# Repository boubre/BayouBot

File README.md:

BayouBot
========

Software for controlling an inexpensive educational robot.

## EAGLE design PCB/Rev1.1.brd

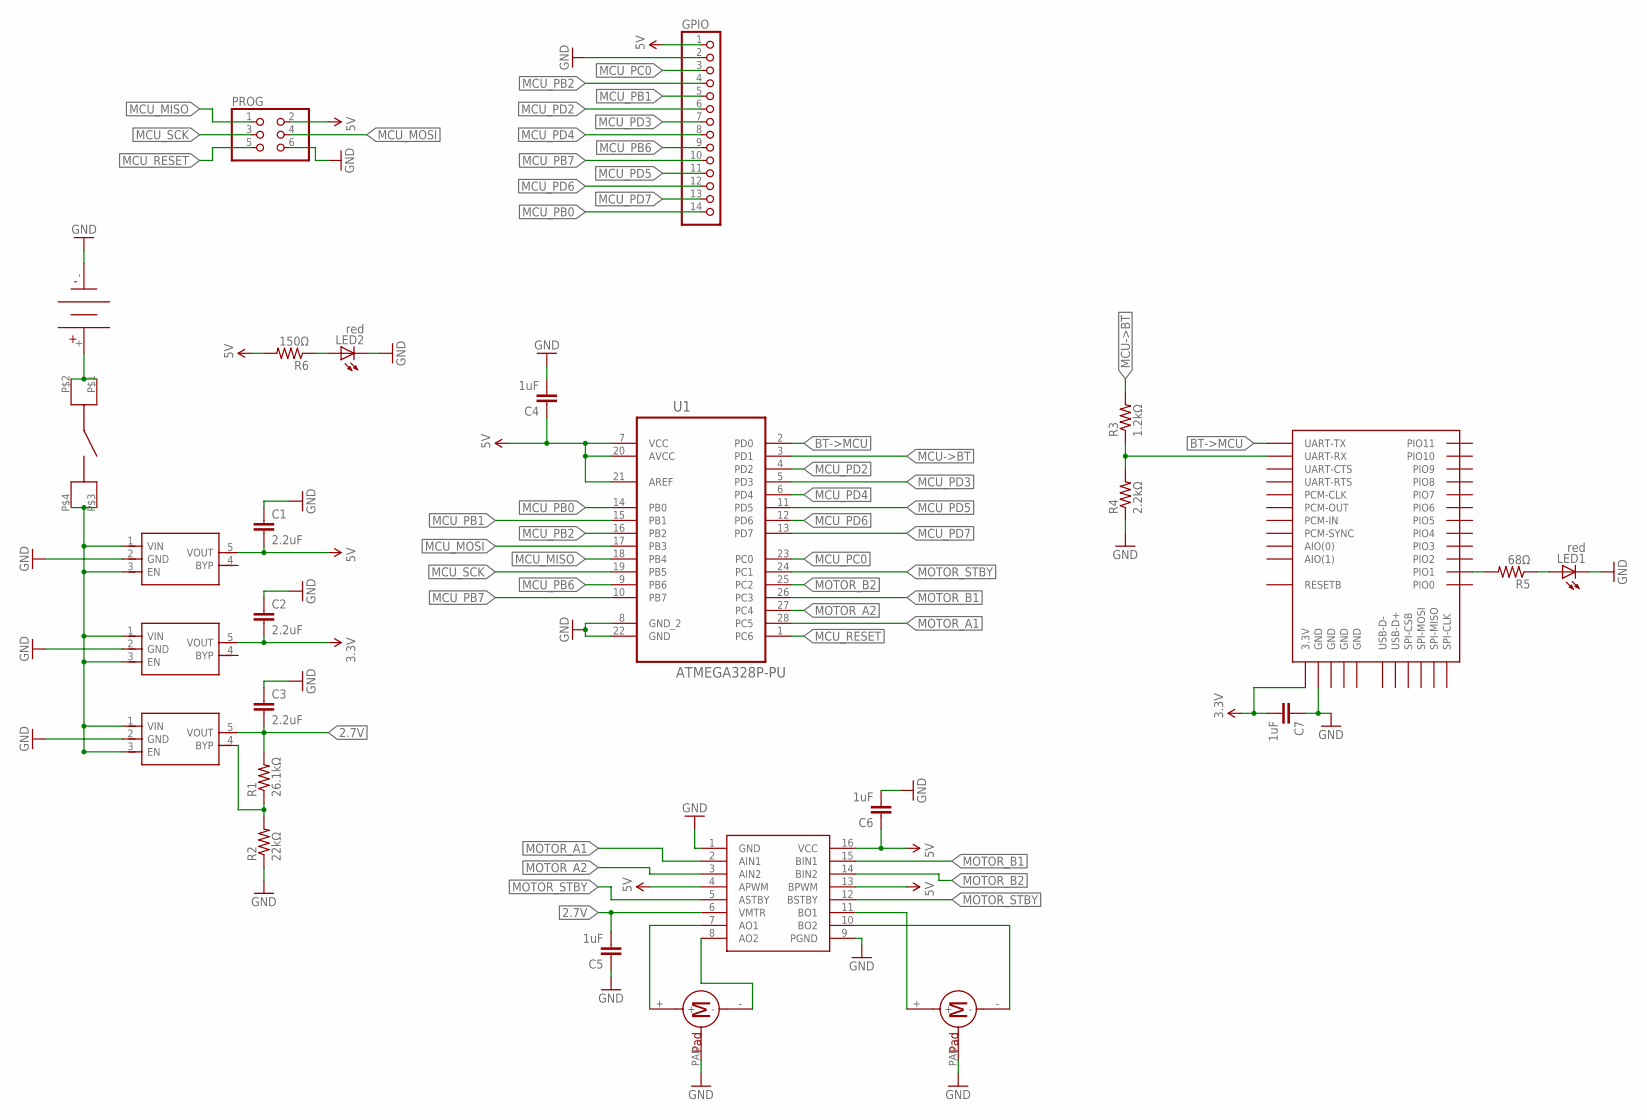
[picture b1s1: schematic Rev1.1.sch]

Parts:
C1, C2, C3: 2.2uF; 0805
C4, C5, C6, C7: 1uF; 0805
GPIO: PINHD-1X14; 1X14
LED1, LED2: red; CHIP-LED0805
PROG: PINHD-2X3; 2X03
R1: 26.1kΩ; 0805
R2: 22kΩ; 0805
R3: 1.2kΩ; 0805
R4: 2.2kΩ; 0805
R5: 68Ω; 0805
R6: 150Ω; 0805
U1: ATMEGA328P-PU; DIP254P762X457-28
U2: BT; BTM400_6B
U3: SMD_H-BRIDGE; SSOP16
U$1: 20MM_COIN
U$2: POWER_BTN
U$3: 5V Reg; SOT23-5
U$4: 3.3V Reg; SOT23-5
U$5: 2.7V Reg; SOT23-5
U$7, U$8: PICO_VIBE_MTR

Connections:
2.7V: C3.2, C5.2, R1.2, U3.6 (VMTR), U$5.5 (VOUT)
3.3V: C2.2, C7.2, U2.3.3V, U$4.5 (VOUT)
5V: C1.2, C4.1, C6.1, GPIO.1, PROG.2, R6.2, U1.7 (VCC), U1.20 (AVCC), U1.21 (AREF), U3.4 (APWM), U3.13 (BPWM), U3.16 (VCC), U$3.5 (VOUT)
BT->MCU: U1.2 (PD0), U2.UART-TX
GND: C1.1, C2.1, C3.1, C4.2, C5.1, C6.2, C7.1, GPIO.2, LED1.C, LED2.C, PROG.6, R2.1, R4.1, U1.8 (GND_2), U1.22 (GND), U2.GND@1 (GND), U2.GND@2 (GND), U2.GND@3 (GND), U2.GND@4 (GND), U3.1 (GND), U3.9 (PGND), U$1.-, U$3.2 (GND), U$4.2 (GND), U$5.2 (GND), U$7.PAD, U$8.PAD
MCU->BT: R3.2, U1.3 (PD1)
MCU_MISO: PROG.1, U1.18 (PB4)
MCU_MOSI: PROG.4, U1.17 (PB3)
MCU_PB0: GPIO.14, U1.14 (PB0)
MCU_PB1: GPIO.5, U1.15 (PB1)
MCU_PB2: GPIO.4, U1.16 (PB2)
MCU_PB6: GPIO.9, U1.9 (PB6)
MCU_PB7: GPIO.10, U1.10 (PB7)
MCU_PC0: GPIO.3, U1.23 (PC0)
MCU_PD2: GPIO.6, U1.4 (PD2)
MCU_PD3: GPIO.7, U1.5 (PD3)
MCU_PD4: GPIO.8, U1.6 (PD4)
MCU_PD5: GPIO.11, U1.11 (PD5)
MCU_PD6: GPIO.12, U1.12 (PD6)
MCU_PD7: GPIO.13, U1.13 (PD7)
MCU_RESET: PROG.5, U1.1 (PC6)
MCU_SCK: PROG.3, U1.19 (PB5)
MOTOR_A1: U1.28 (PC5), U3.2 (AIN1)
MOTOR_A2: U1.27 (PC4), U3.3 (AIN2)
MOTOR_B1: U1.26 (PC3), U3.15 (BIN1)
MOTOR_B2: U1.25 (PC2), U3.14 (BIN2)
MOTOR_STBY: U1.24 (PC1), U3.5 (ASTBY), U3.12 (BSTBY)
unnamed: U$1.+, U$2.P$1, U$2.P$2
unnamed: U$2.P$3, U$2.P$4, U$3.1 (VIN), U$3.3 (EN), U$4.1 (VIN), U$4.3 (EN), U$5.1 (VIN), U$5.3 (EN)
unnamed: R1.1, R2.2, U$5.4 (BYP)
unnamed: U3.7 (AO1), U$7.+
unnamed: U3.8 (AO2), U$7.-
unnamed: U3.11 (BO1), U$8.+
unnamed: U3.10 (BO2), U$8.-
unnamed: R3.1, R4.2, U2.UART-RX
unnamed: R5.2, U2.PIO(1) (PIO1)
unnamed: LED1.A, R5.1
unnamed: LED2.A, R6.1

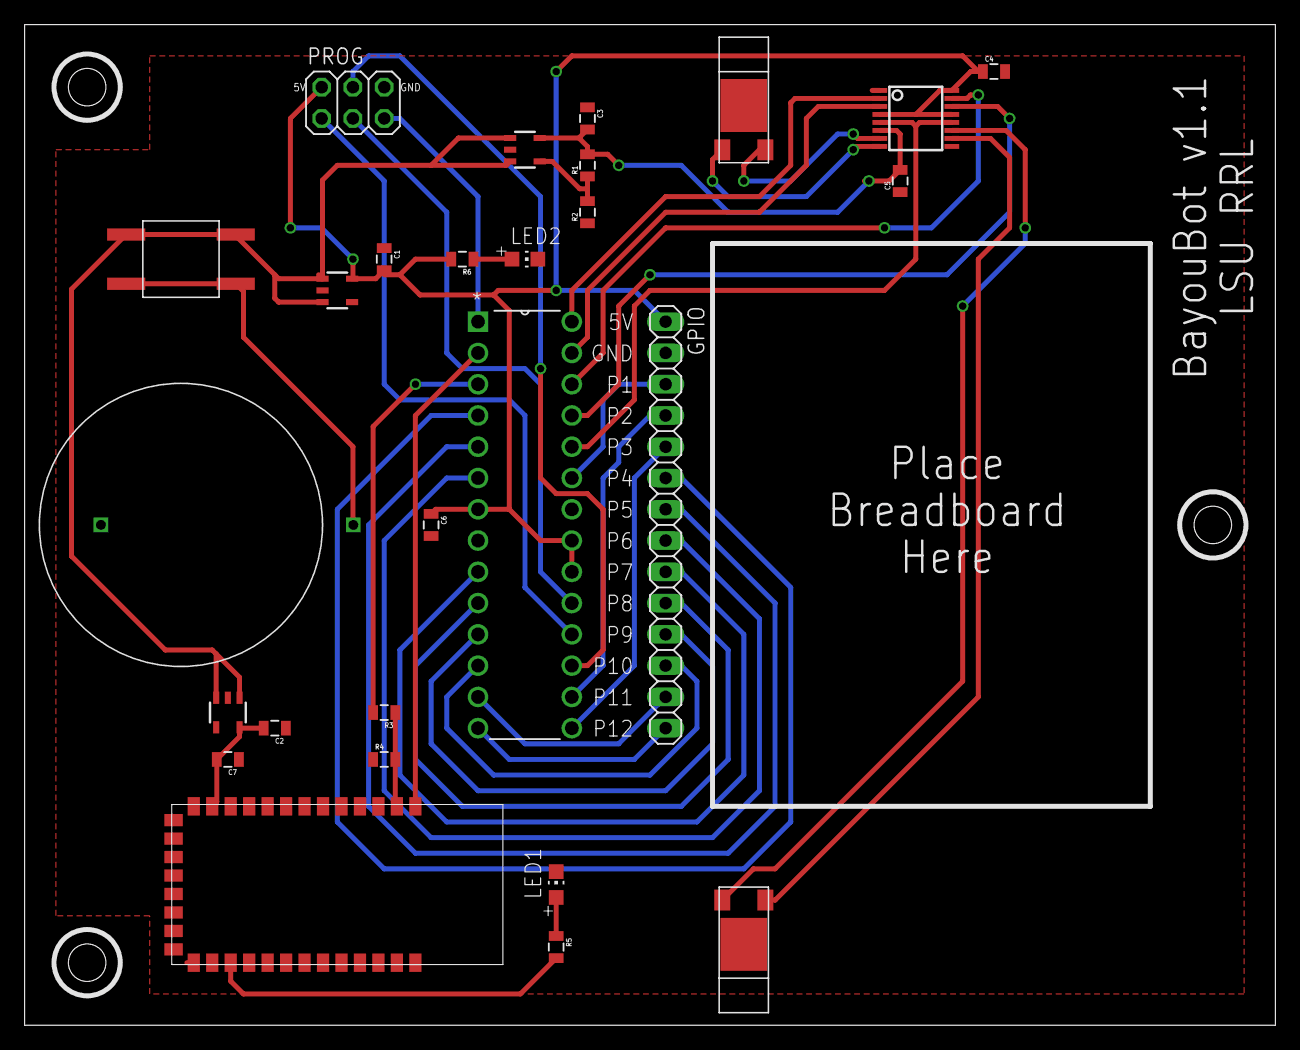
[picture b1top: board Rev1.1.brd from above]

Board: 2 copper layers, 101.6 x 81.3 mm, 27 parts (0 on the bottom side), 38 nets.

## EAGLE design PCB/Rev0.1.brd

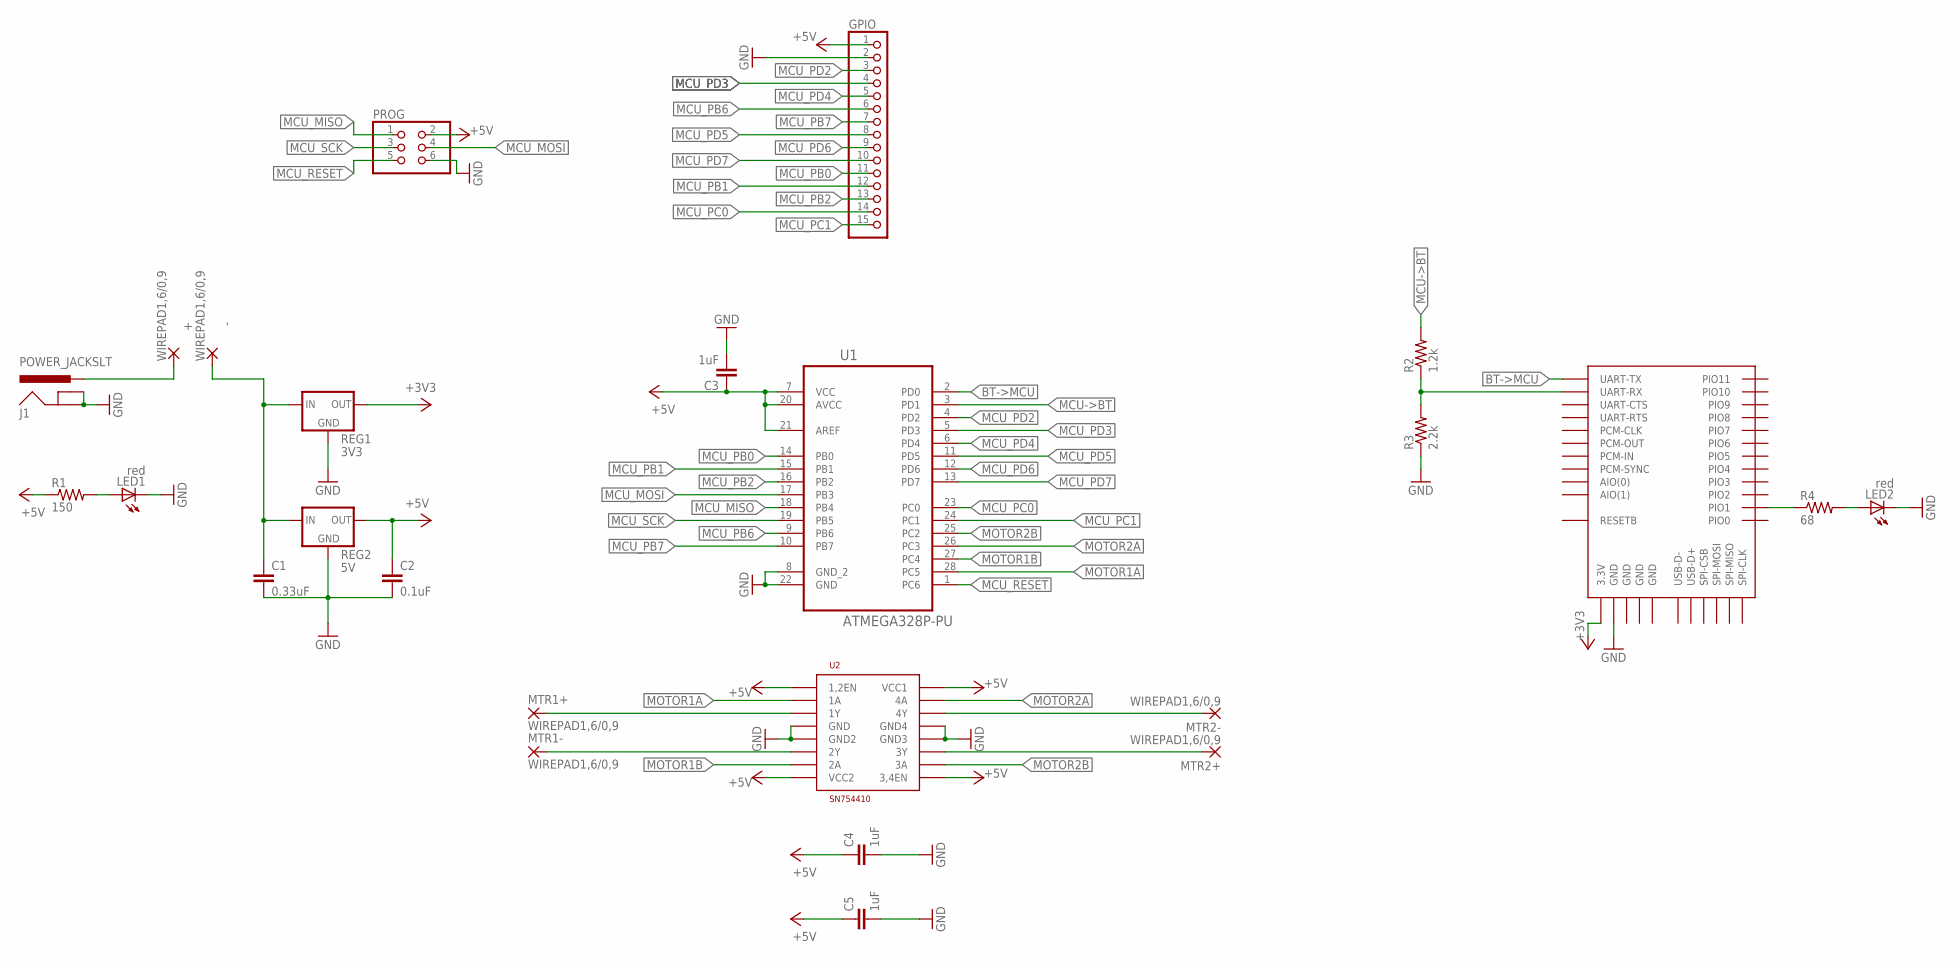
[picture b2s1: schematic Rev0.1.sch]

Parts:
+: WIREPAD1,6/0,9; 1,6/0,9
-: WIREPAD1,6/0,9; 1,6/0,9
C1: 0.33uF; 0805
C2: 0.1uF; 0805
C3, C4, C5: 1uF; 0805
GPIO: PINHD-1X15; 1X15
J1: POWER_JACKSLT; POWER_JACK_SLOT
LED1, LED2: red; CHIP-LED0805
MTR1+, MTR1-, MTR2+, MTR2-: WIREPAD1,6/0,9; 1,6/0,9
PROG: PINHD-2X3; 2X03
R1: 150; R0805
R2: 1.2k; R0805
R3: 2.2k; R0805
R4: 68; R0805
REG1: 3V3; TO220V
REG2: 5V; TO220V
U1: ATMEGA328P-PU; DIP254P762X457-28
U2: H-BRIDGE; DIP16
U$1: BTM400_6B

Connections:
+3V3: REG1.3 (OUT), U$1.3.3V
+5V: C2.1, C3.1, C4.1, C5.1, GPIO.1, PROG.2, R1.1, REG2.3 (OUT), U1.7 (VCC), U1.20 (AVCC), U1.21 (AREF), U2.P$1 (1,2EN), U2.P$8 (VCC2), U2.P$9 (3,4EN), U2.P$16 (VCC1)
BT->MCU: U1.2 (PD0), U$1.UART-TX
GND: C1.2, C2.2, C3.2, C4.2, C5.2, GPIO.2, J1.GND@1 (GNDBREAK), J1.GND@2 (GND), LED1.C, LED2.C, PROG.6, R3.1, REG1.2 (GND), REG2.2 (GND), U1.8 (GND_2), U1.22 (GND), U2.P$4 (GND), U2.P$5 (GND2), U2.P$12 (GND3), U2.P$13 (GND4), U$1.GND@1 (GND), U$1.GND@2 (GND), U$1.GND@3 (GND), U$1.GND@4 (GND)
MCU->BT: R2.2, U1.3 (PD1)
MCU_MISO: PROG.1, U1.18 (PB4)
MCU_MOSI: PROG.4, U1.17 (PB3)
MCU_PB0: GPIO.11, U1.14 (PB0)
MCU_PB1: GPIO.12, U1.15 (PB1)
MCU_PB2: GPIO.13, U1.16 (PB2)
MCU_PB6: GPIO.6, U1.9 (PB6)
MCU_PB7: GPIO.7, U1.10 (PB7)
MCU_PC0: GPIO.14, U1.23 (PC0)
MCU_PC1: GPIO.15, U1.24 (PC1)
MCU_PD2: GPIO.3, U1.4 (PD2)
MCU_PD3: GPIO.4, U1.5 (PD3)
MCU_PD4: GPIO.5, U1.6 (PD4)
MCU_PD5: GPIO.8, U1.11 (PD5)
MCU_PD6: GPIO.9, U1.12 (PD6)
MCU_PD7: GPIO.10, U1.13 (PD7)
MCU_RESET: PROG.5, U1.1 (PC6)
MCU_SCK: PROG.3, U1.19 (PB5)
MOTOR1A: U1.28 (PC5), U2.P$2 (1A)
MOTOR1B: U1.27 (PC4), U2.P$7 (2A)
MOTOR2A: U1.26 (PC3), U2.P$15 (4A)
MOTOR2B: U1.25 (PC2), U2.P$10 (3A)
unnamed: -.1, C1.1, REG1.1 (IN), REG2.1 (IN)
unnamed: LED1.A, R1.2
unnamed: +.1, J1.PWR
unnamed: MTR1+.1, U2.P$3 (1Y)
unnamed: MTR1-.1, U2.P$6 (2Y)
unnamed: MTR2-.1, U2.P$14 (4Y)
unnamed: MTR2+.1, U2.P$11 (3Y)
unnamed: R2.1, R3.2, U$1.UART-RX
unnamed: R4.1, U$1.PIO(1) (PIO1)
unnamed: LED2.A, R4.2

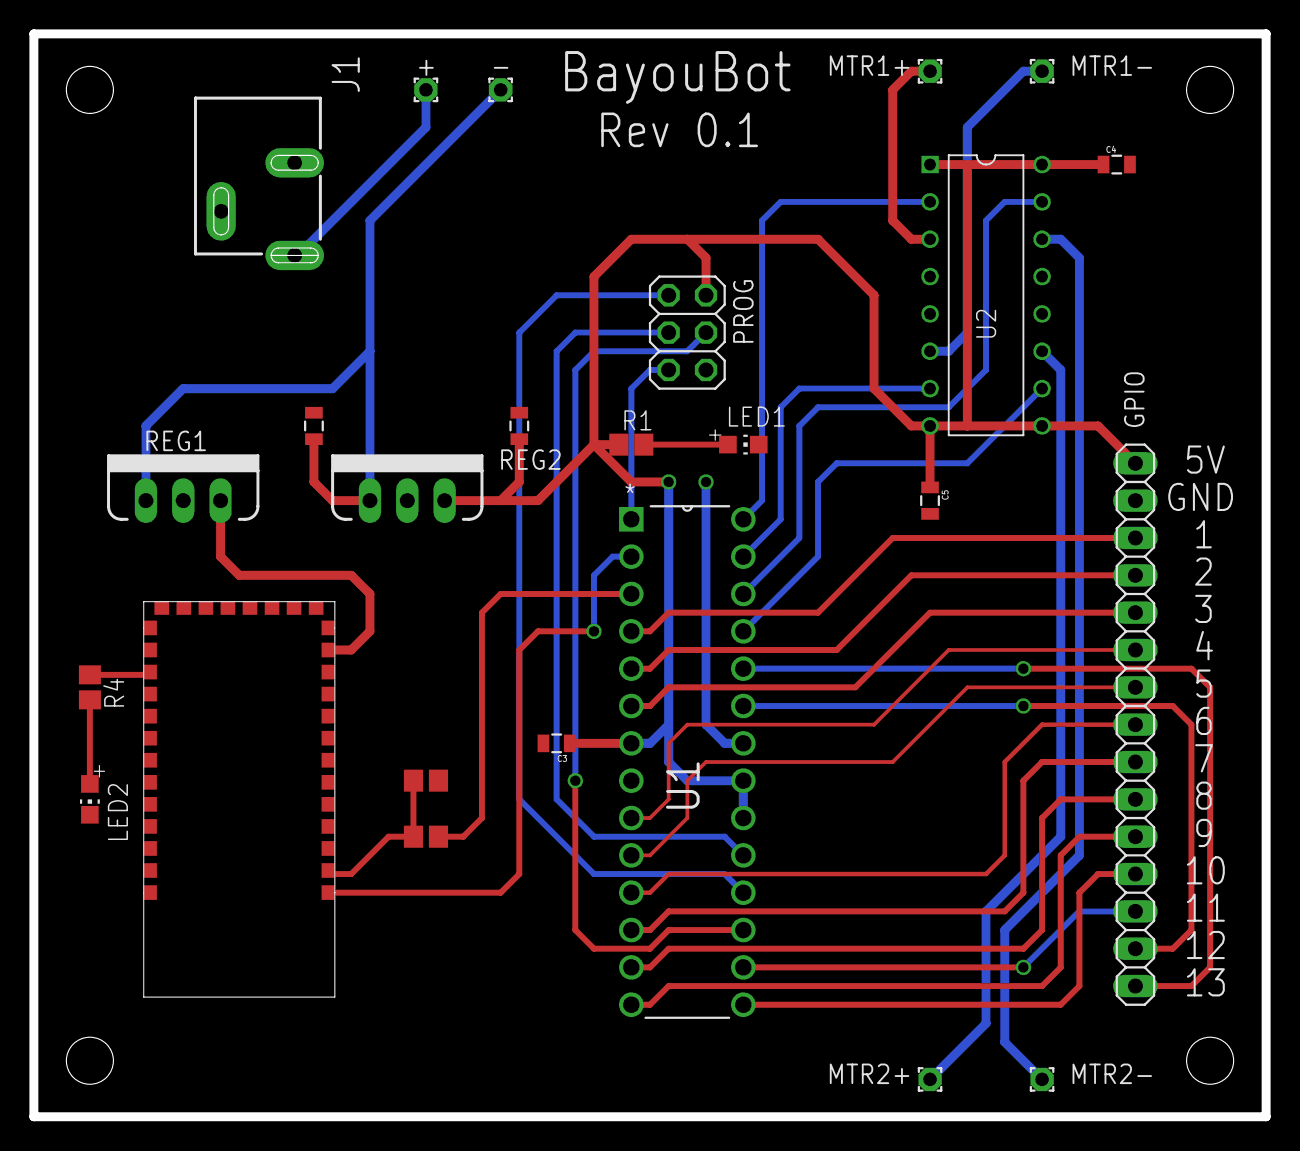
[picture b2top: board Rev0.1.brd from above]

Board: 2 copper layers, 83.8 x 73.7 mm, 25 parts (0 on the bottom side), 36 nets.

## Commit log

2013-09-23 Create gh-pages branch via GitHub
2013-09-23 Added Java Core Library
2013-09-23 Added Firmware files
2013-09-23 Device Discovery Test
2013-09-23 Added dependency jar for Bluetooth
2013-09-25 Tested serial comms by changing name of BT Device.
2013-09-27 Updated Firmware Project Structure.
2013-09-27 USART and Util libraries filled out.
2013-09-30 Restructured Device Discovery example so that it can be used by the program at a later time.
2013-09-30 Firmware readied for echo test.
2013-09-30 Service Detection Implemented
2013-10-02 Java side of working Bluetooth echo.
2013-10-02 Firmware side of working Bluetooth echo server. Also fixed a small bug if Util_writeStr()
2013-10-07 Started Documentation folder for Latex source
2013-10-09 Set up basic BayouBot API and wrote a blinking light test.
2013-10-14 Firmware Interpreter Responds to GPIO commands
2013-10-14 Test to flash LED using BayouBot class.
2013-10-14 Firmware supports read and reset operations.
2013-10-14 Added hardware query and reset capabilities. Also added javadoc comments to code.
2013-10-23 Added movement function declarations.
2014-02-11 Added drive commands to support new circuit addition. Updated documentation accordingly.
2014-02-17 Started PCB Design
2014-02-19 Added Bluetooth Part, Further Wiring
2014-02-24 Finished Schematic Design. Translated to PCB.
2014-02-26 Finished PCB Design
2014-09-12 Changed from DesignSpark to Eagle. Ready for board prototype submission.
2014-09-12 Added some silkscreen text.
2014-09-14 Added parts spreadsheet, which catalogues robot parts and their prices at varies purchase quantities.
2014-11-10 Added firmware code that renames the Bluetooth chip to BayoutBot.
2014-12-27 Added OpenBlocks source into project. The BayouBot Workspace will used OpenBlocks as the graphical engine for a block-based programming language.
2014-12-27 Added barebones language def file. Changed workspace title.
2014-12-27 Added more basic block types to the language.
2014-12-28 Added Console to workspace.
2014-12-28 Forgot to add JavaDoc comments to Console.
2014-12-28 Added several features to WorkspaceController and ensured that Console functions are always correctly invoked on event dispatcher thread.
2014-12-29 Added some Execution thread functionality.
2014-12-29 Basic code for the beginning of a program parse.
2014-12-30 Added more parse functionality.
2014-12-31 Completed the parse tree for the current langauge subset.
2014-12-31 Forgot to refresh and include minor language refactoring.
2014-12-31 Decided to simplify numbers to just double values. May add different numnber types in the future if deemed necessary.
2014-12-31 Added math-related blocks to the the block language.
2014-12-31 Refactoring to greatly simplify parsing. Added friendlyName property to each genus. Added basic arithmetic operation parse code.
2015-01-01 Did slight refactoring of errors and warnings that will allow for a more robust interface later on.
2015-01-01 Slight refactoring of functions to reduce code duplication.
2015-01-01 Added parse code for math functionality.
2015-02-08 Added Logic section. Added function to handle pasring chained commands as support for the If command as well as for future functions such as loops and procedures.
2015-02-09 Added code for variable support.
2015-02-09 Added string equals and not equals functions.
2015-02-10 Added repeat and while loops.
2015-02-23 Added SOT23-5 device for SMD linear voltage regulators. Extended pads on Bluetooth transceiver so that soldering the next board revision will be easier.
2015-02-23 Added smd h bridge and vibration motor devices.
2015-02-23 Added gitignore for eagle autosaves.
2015-02-23 Added 20mm coin cell battery holder footprint.
2015-02-24 Added pushbutton part and started schematic for new board revision.
2015-02-24 Finished power supply schematic.
2015-02-25 Finished schematic for next board revision.
2015-02-25 Updated PCB parts documentation for new version.
2015-02-25 Updated a part.
2015-02-26 Routed new PCB version.
2015-02-26 Minor Board Changes
2015-02-26 Clearance Hotfix
2015-02-26 Moved power button to better location.
2015-02-26 Moved ground pour to top copper to get rid of many vias needed for the SMD components.
2015-03-02 Moved JavaCore compliance up to 1.8. Included jSSC with intent of treating Bluetooth devices as serial ports.
2015-03-02 Added README on how to connect Bluetooth SPP to a virtual serial port and deleted Test2.
2015-03-02 Added some basic (incomplete) code for the bluetooth over virtual serial port bayou bot. Confirmed functionality of what was written.
2015-03-02 Added dependencies for the workspace that were accidently culled by the gitignore.
2015-03-25 Changed pin enum to reflect new pin configuration.
2015-03-27 Added BayouBot features to the language definition. These features still need parser implementation.
2015-03-28 Added parsing code for robot-related blocks. Added sleep command and main loop (previously called runtime) procedure. Simplified unqiue procedure code. (& Got rid of Setup class.)
2015-03-28 Added procedures to the workspace langauge. Also added listSerialPort method to the serial port bayou bot so that clients do not need to explicity call jssc.
2015-03-28 Added Dummy Bayou Bot as well as the ability to check code without running an execution.
2015-03-28 Added the serial port drop down box to the workspace.
2015-04-01 Made the workspace show up on my laptop. Fixed a null poiner exception where caused by calling a parse dump on a null progra, returned from parse.
2015-04-01 Minor changes to clean up some code from OpenBlocks.
2015-04-01 Implemented program execution. Fixed set variable bug that led to infinite recursion.
2015-04-01 Added menu bar with save and load functions. Added status label for BayouBot connection status.
2015-04-01 Changed order and coloration of block drawers and blocks.

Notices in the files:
parts and their libraries:
SparkFun-Capacitors: Licensing: Creative Commons ShareAlike 4.0 International - https://creativecommons.org/licenses/by-sa/4.0
